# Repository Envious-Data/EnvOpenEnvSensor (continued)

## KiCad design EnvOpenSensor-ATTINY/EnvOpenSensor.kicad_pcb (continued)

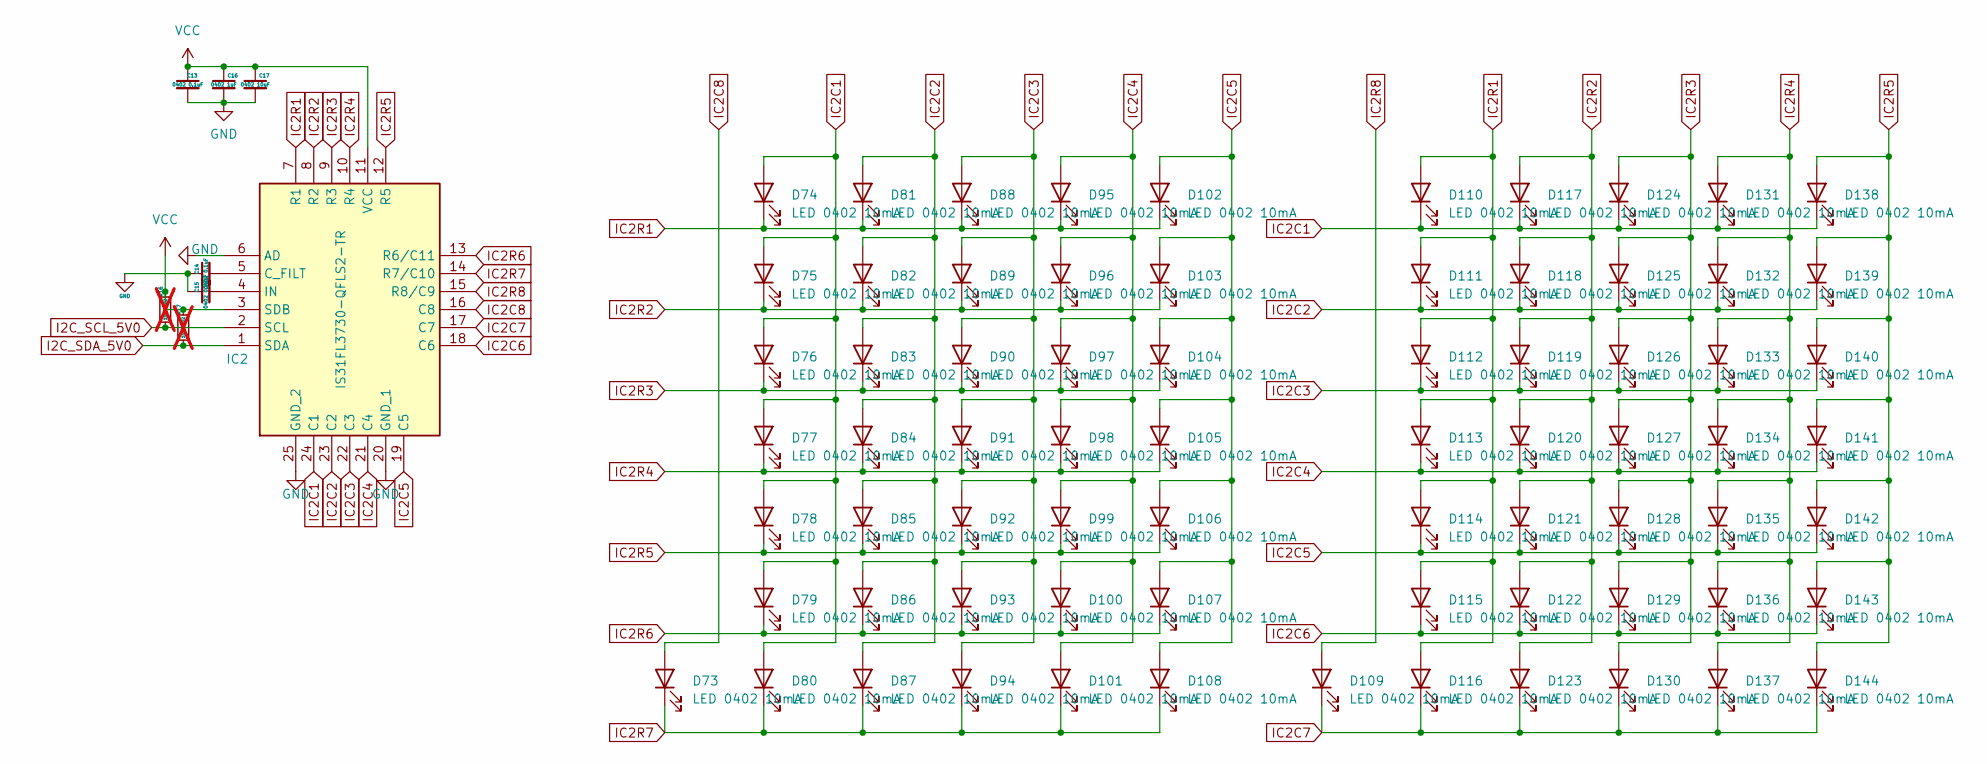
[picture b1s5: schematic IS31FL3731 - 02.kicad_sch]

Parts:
C13, C14: 0402 0.1uF; C_0402_1005Metric
C15: 0402 0.22uF; C_0402_1005Metric
C16: 0402 1uF; C_0402_1005Metric
C17: 0402 10uF; C_0402_1005Metric
D73, D74, D75, D76, D77, D78, D79, D80, D81, D82, D83, D84, D85, D86, D87, D88, D89, D90, D91, D92, D93, D94, D95, D96, D97, D98, D99, D100, D101, D102, D103, D104, D105, D106, D107, D108, D109, D110, D111, D112, D113, D114, D115, D116, D117, D118, D119, D120, D121, D122, D123, D124, D125, D126, D127, D128, D129, D130, D131, D132, D133, D134, D135, D136, D137, D138, D139, D140, D141, D142, D143, D144: LED 0402 10mA; LED_0402_1005Metric
IC2: IS31FL3730-QFLS2-TR; QFN-24-1EP_4x4mm_P0.5mm_EP2.6x2.6mm_ThermalVias; Mouser Part Number 870-IS31FL3730QFLS2R
R16, R17: 10K 0402; R_0402_1005Metric; not fitted

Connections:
GND: C13.2, C14.1, C15.1, C16.2, C17.2, IC2.6 (AD), IC2.20 (GND_1), IC2.25 (GND_2); also elsewhere on the board
I2C_SCL_5V0: IC2.2 (SCL), R16.1; also elsewhere on the board
I2C_SDA_5V0: IC2.1 (SDA), R17.1; also elsewhere on the board
IC2C1: D74.2 (A), D75.2 (A), D76.2 (A), D77.2 (A), D78.2 (A), D79.2 (A), D80.2 (A), D110.1 (K), D117.1 (K), D124.1 (K), D131.1 (K), D138.1 (K), IC2.24 (C1)
IC2C2: D81.2 (A), D82.2 (A), D83.2 (A), D84.2 (A), D85.2 (A), D86.2 (A), D87.2 (A), D111.1 (K), D118.1 (K), D125.1 (K), D132.1 (K), D139.1 (K), IC2.23 (C2)
IC2C3: D88.2 (A), D89.2 (A), D90.2 (A), D91.2 (A), D92.2 (A), D93.2 (A), D94.2 (A), D112.1 (K), D119.1 (K), D126.1 (K), D133.1 (K), D140.1 (K), IC2.22 (C3)
IC2C4: D95.2 (A), D96.2 (A), D97.2 (A), D98.2 (A), D99.2 (A), D100.2 (A), D101.2 (A), D113.1 (K), D120.1 (K), D127.1 (K), D134.1 (K), D141.1 (K), IC2.21 (C4)
IC2C5: D102.2 (A), D103.2 (A), D104.2 (A), D105.2 (A), D106.2 (A), D107.2 (A), D108.2 (A), D114.1 (K), D121.1 (K), D128.1 (K), D135.1 (K), D142.1 (K), IC2.19 (C5)
IC2C6: D115.1 (K), D122.1 (K), D129.1 (K), D136.1 (K), D143.1 (K), IC2.18 (C6)
IC2C7: D109.1 (K), D116.1 (K), D123.1 (K), D130.1 (K), D137.1 (K), D144.1 (K), IC2.17 (C7)
IC2C8: D73.2 (A), IC2.16 (C8)
IC2R1: D74.1 (K), D81.1 (K), D88.1 (K), D95.1 (K), D102.1 (K), D110.2 (A), D111.2 (A), D112.2 (A), D113.2 (A), D114.2 (A), D115.2 (A), D116.2 (A), IC2.7 (R1)
IC2R2: D75.1 (K), D82.1 (K), D89.1 (K), D96.1 (K), D103.1 (K), D117.2 (A), D118.2 (A), D119.2 (A), D120.2 (A), D121.2 (A), D122.2 (A), D123.2 (A), IC2.8 (R2)
IC2R3: D76.1 (K), D83.1 (K), D90.1 (K), D97.1 (K), D104.1 (K), D124.2 (A), D125.2 (A), D126.2 (A), D127.2 (A), D128.2 (A), D129.2 (A), D130.2 (A), IC2.9 (R3)
IC2R4: D77.1 (K), D84.1 (K), D91.1 (K), D98.1 (K), D105.1 (K), D131.2 (A), D132.2 (A), D133.2 (A), D134.2 (A), D135.2 (A), D136.2 (A), D137.2 (A), IC2.10 (R4)
IC2R5: D78.1 (K), D85.1 (K), D92.1 (K), D99.1 (K), D106.1 (K), D138.2 (A), D139.2 (A), D140.2 (A), D141.2 (A), D142.2 (A), D143.2 (A), D144.2 (A), IC2.12 (R5)
IC2R6: D79.1 (K), D86.1 (K), D93.1 (K), D100.1 (K), D107.1 (K), IC2.13 (R6/C11)
IC2R7: D73.1 (K), D80.1 (K), D87.1 (K), D94.1 (K), D101.1 (K), D108.1 (K), IC2.14 (R7/C10)
IC2R8: D109.2 (A), IC2.15 (R8/C9)
unnamed: C14.2, IC2.5 (C_FILT)
unnamed: C15.2, IC2.4 (IN)
VCC: C13.1, C16.1, C17.1, IC2.3 (SDB), IC2.11 (VCC), R16.2, R17.2; also elsewhere on the board

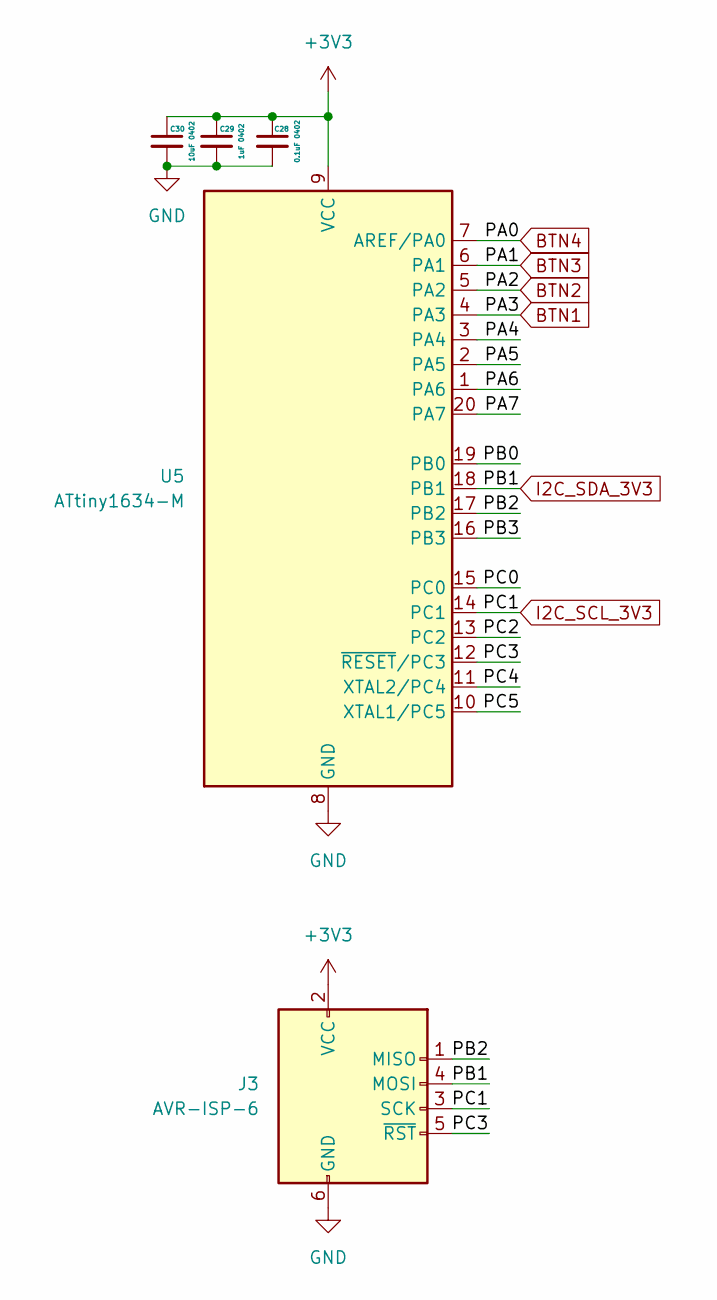
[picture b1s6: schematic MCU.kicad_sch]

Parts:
C28: 0.1uF 0402; C_0402_1005Metric
C29: 1uF 0402; C_0402_1005Metric
C30: 10uF 0402; C_0402_1005Metric
J3: AVR-ISP-6; IDC-Header_2x03_P2.54mm_Vertical
U5: ATtiny1634-M; QFN-20-1EP_4x4mm_P0.5mm_EP2.6x2.6mm

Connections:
+3V3: C28.1, C29.1, C30.1, J3.2 (VCC), U5.9 (VCC); also elsewhere on the board
/MCU/PA4: U5.3 (PA4)
/MCU/PA5: U5.2 (PA5)
/MCU/PA6: U5.1 (PA6)
/MCU/PA7: U5.20 (PA7)
/MCU/PB0: U5.19 (PB0)
/MCU/PB2: J3.1 (MISO), U5.17 (PB2)
/MCU/PB3: U5.16 (PB3)
/MCU/PC0: U5.15 (PC0)
/MCU/PC2: U5.13 (PC2)
/MCU/PC3: J3.5 (~RST), U5.12 (~RESET/PC3)
/MCU/PC4: U5.11 (XTAL2/PC4)
/MCU/PC5: U5.10 (XTAL1/PC5)
BTN1: U5.4 (PA3); also elsewhere on the board
BTN2: U5.5 (PA2); also elsewhere on the board
BTN3: U5.6 (PA1); also elsewhere on the board
BTN4: U5.7 (AREF/PA0); also elsewhere on the board
GND: C28.2, C29.2, C30.2, J3.6 (GND), U5.8 (GND), U5.21 (GND); also elsewhere on the board
I2C_SCL_3V3: J3.3 (SCK), U5.14 (PC1); also elsewhere on the board
I2C_SDA_3V3: J3.4 (MOSI), U5.18 (PB1); also elsewhere on the board

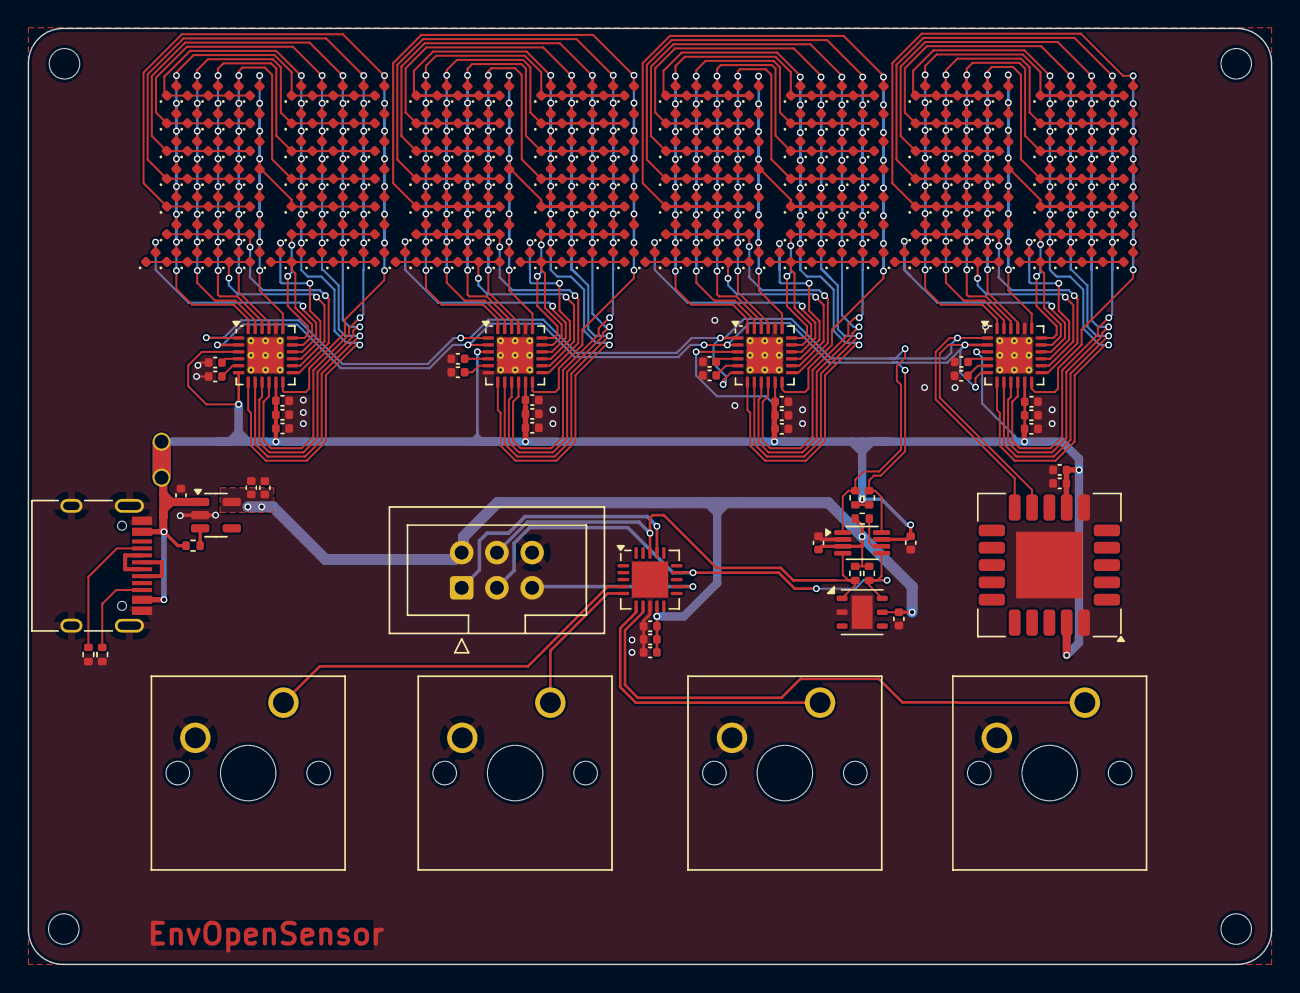
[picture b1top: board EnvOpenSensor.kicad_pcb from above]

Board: 2 copper layers, 89.7 x 67.5 mm, 347 parts (0 on the bottom side), 92 nets.

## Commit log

2024-03-28 added files and started work on design.
2024-03-28 forgot some stuff
2024-03-28 added 3d models and shuffled some parts about for better usability.
2024-03-29 added DIY305 models
2024-03-30 commit current version
2024-03-31 let autorouter go crazy
2024-03-31 clearanced the matrix
2024-03-31 generated production files
2024-03-31 updated production files and silkscreen
2024-04-01 began re-work on fixing colossal mistakes
2024-04-01 re-did the PCB
2024-06-05 swapped LDO for more capable switching regulator
2024-06-07 added pin labels and some corrections to layout.
2024-06-07 re-drew all traces and moved some components about
2024-09-07 recognised issues with the design, redid schematic to include onboard LEDs and a RP2040, started re-work on PCB
2024-09-08 finished routing up board, needs a double-check
2024-09-08 moved reset button - easier to access, added button labels, wired up switches
2024-09-12 Added level shifter IC and fixed incorrect wiring + label
2024-09-12 corrected a couple small issues
2024-11-20 Made ATTINY1684 version.
2024-11-20 made a few corrections to duplicated vias and trace routing
2024-11-21 added pullup to reset (schematic only)
